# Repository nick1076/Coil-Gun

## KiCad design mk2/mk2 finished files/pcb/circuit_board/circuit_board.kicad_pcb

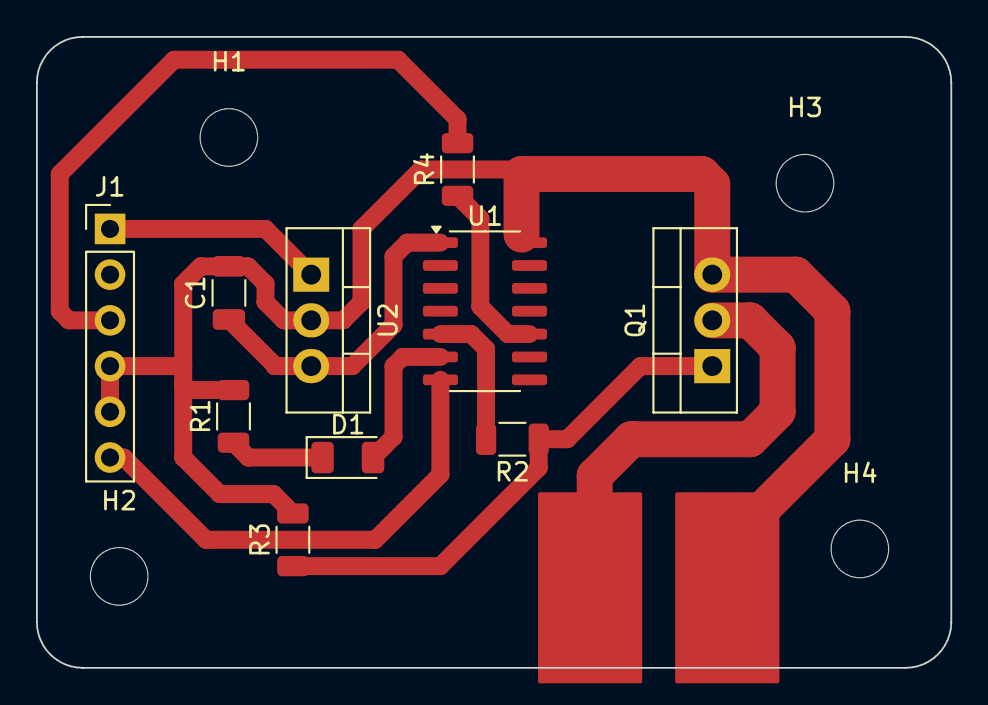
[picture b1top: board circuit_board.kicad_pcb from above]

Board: 2 copper layers, 50.8 x 35.1 mm, 14 parts (0 on the bottom side), 10 nets.

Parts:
C1: 100µF; C_1206_3216Metric
D1: LED; LED_1206_3216Metric
H1, H2, H3, H4: MountingHole; MountingHole_3.2mm_M3
J1: 2x3 Header; PinHeader_1x06_P2.54mm_Vertical
Q1: IRLZ44N; TO-220-3_Vertical
R1: 100Ω; R_1206_3216Metric
R2: 10Ω; R_1206_3216Metric
R3: 1kΩ; R_1206_3216Metric
R4: 0Ω; R_1206_3216Metric
U1: ATtiny1614; SOIC-14_3.9x8.7mm_P1.27mm
U2: L7805; TO-220-3_Vertical

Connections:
unnamed: D1.2 (A), U1.6 (PB3//D4)
unnamed: D1.1 (K), R1.1
unnamed: J1.1, U2.1 (IN)
unnamed: J1.3, R4.2
unnamed: C1.2, J1.4, J1.5, Q1.3 (S), R1.2, R3.2, U1.14 (GND), U2.2 (GND)
unnamed: J1.6, U1.7 (PB2//D5)
unnamed: Q1.1 (G), R2.1, R3.1
unnamed: R4.1, U1.10 (PA0//UPDI)
unnamed: R2.2, U1.5 (PA7//D3)
unnamed: C1.1, U1.1 (VCC), U2.3 (OUT)

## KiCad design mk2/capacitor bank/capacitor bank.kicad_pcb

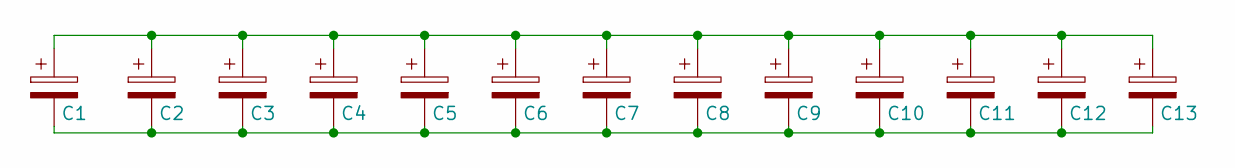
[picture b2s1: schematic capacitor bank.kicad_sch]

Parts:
C1, C2, C3, C4, C5, C6, C7, C8, C9, C10, C11, C12, C13: C_Polarized; CP_Radial_D25.0mm_P10.00mm_SnapIn

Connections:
unnamed: C1.1, C2.1, C3.1, C4.1, C5.1, C6.1, C7.1, C8.1, C9.1, C10.1, C11.1, C12.1, C13.1
unnamed: C1.2, C2.2, C3.2, C4.2, C5.2, C6.2, C7.2, C8.2, C9.2, C10.2, C11.2, C12.2, C13.2

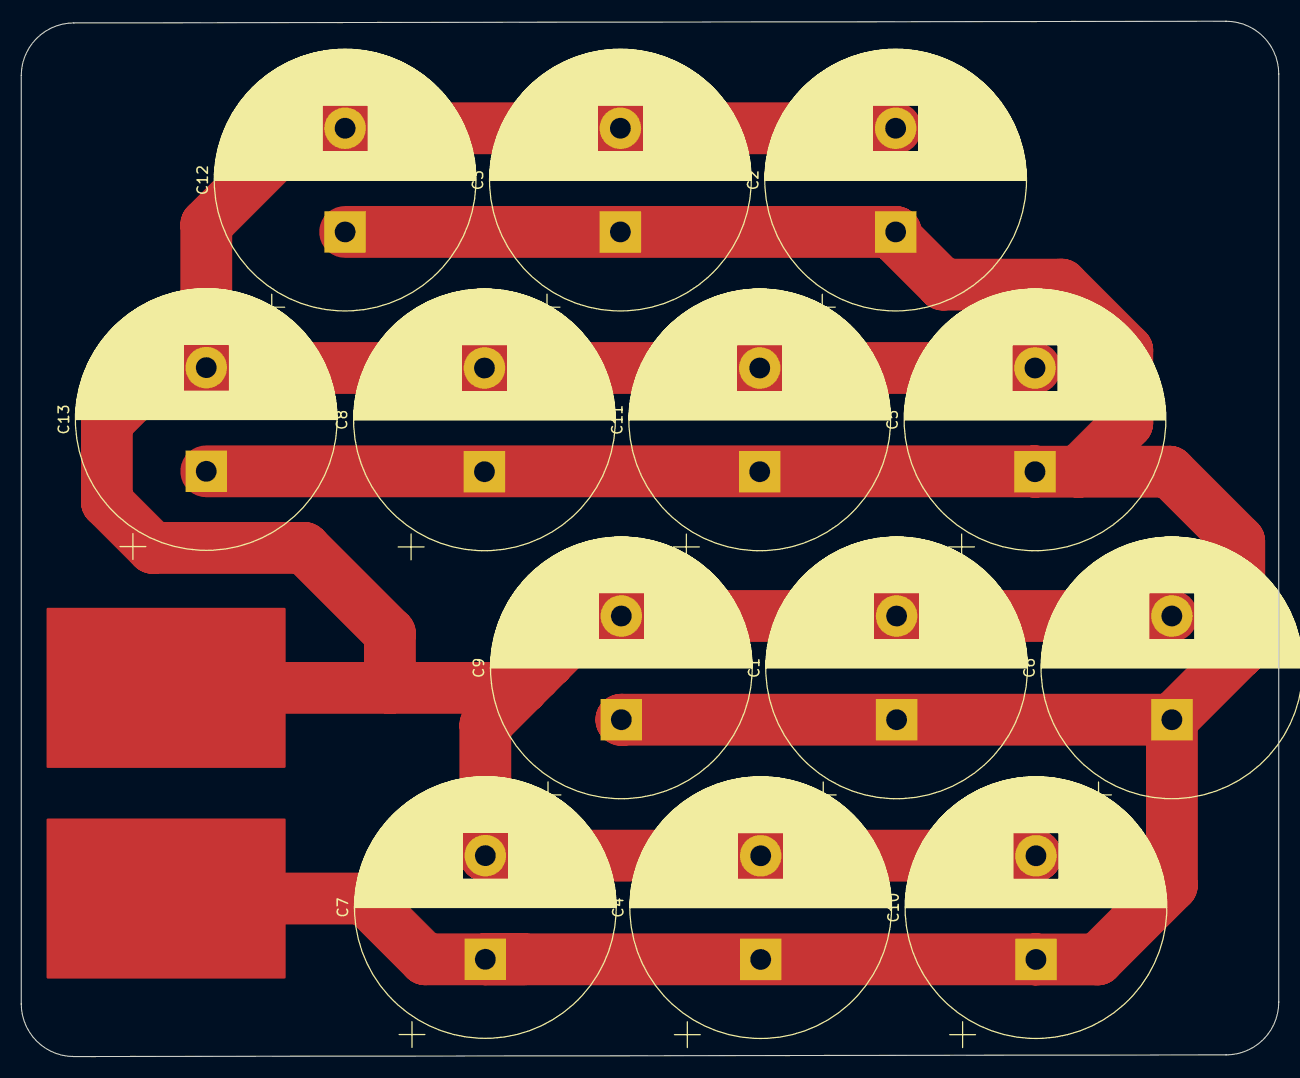
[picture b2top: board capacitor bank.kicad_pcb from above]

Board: 2 copper layers, 121.3 x 99.9 mm, 13 parts (0 on the bottom side), 2 nets.

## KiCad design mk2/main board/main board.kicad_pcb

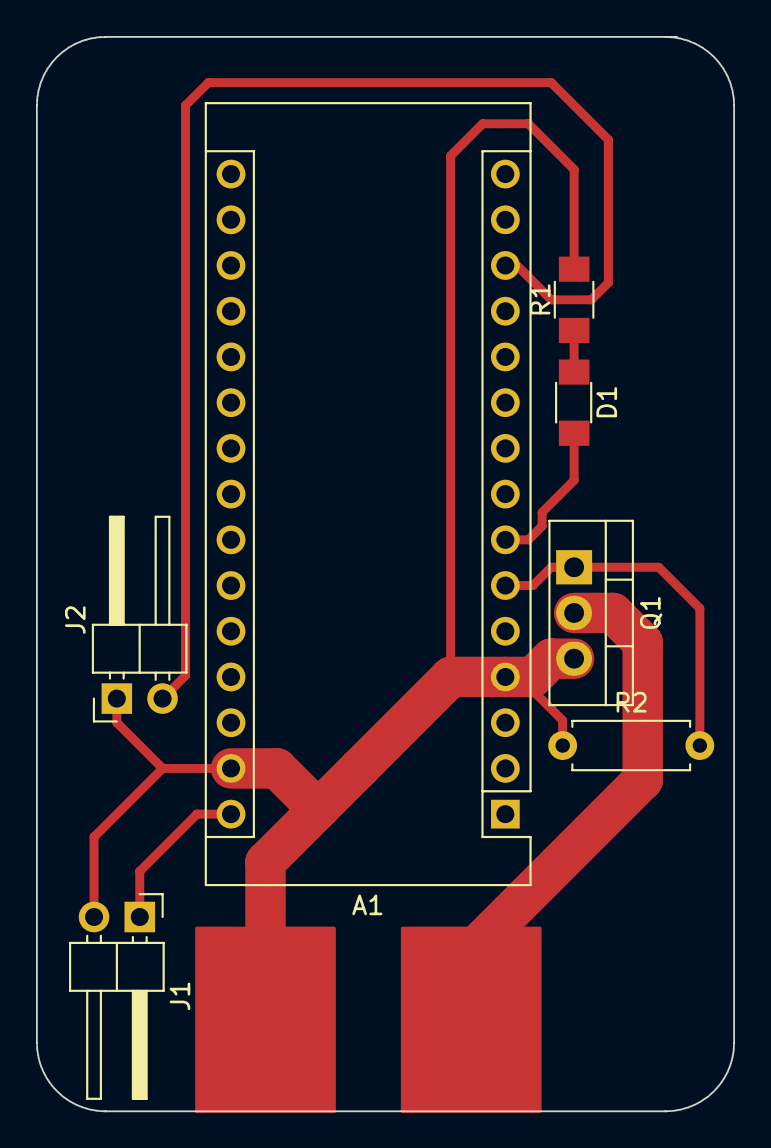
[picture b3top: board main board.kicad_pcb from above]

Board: 2 copper layers, 38.7 x 59.7 mm, 7 parts (0 on the bottom side), 6 nets.

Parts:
A1: Arduino_Nano_Every; Arduino_Nano
D1: LED; LED_1206
J1, J2: Conn_01x02_Male; PinHeader_1x02_P2.54mm_Horizontal
Q1: IRLZ44N; TO-220-3_Vertical
R1: 330; R_1206
R2: 10,000; R_Axial_DIN0207_L6.3mm_D2.5mm_P7.62mm_Horizontal

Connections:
unnamed: A1.6 (D3), Q1.1 (G), R2.2
unnamed: A1.7 (D4), D1.2 (A)
unnamed: A1.13 (D10), J2.2
unnamed: A1.30 (VIN), J1.1
unnamed: D1.1 (K), R1.1
unnamed: A1.4 (GND), A1.29 (GND), J1.2, J2.1, Q1.3 (S), R1.2, R2.1

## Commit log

2024-07-18 KiCad
2024-07-25 Boards - Cap cell & nano board
2024-07-26 PCB Updates
2024-07-26 PCB M3 Hole updates
2024-07-26 Work updates
2024-07-26 Board Updates (Simplification)
2024-07-28 Working Mk2 PCB, Code, & Models
2024-08-01 Mk2 updates
2024-08-01 Circuit Board Edits
2024-08-01 Cleanup
2024-08-02 PCB Pinout Rework
2024-10-18 Altium implimentation
